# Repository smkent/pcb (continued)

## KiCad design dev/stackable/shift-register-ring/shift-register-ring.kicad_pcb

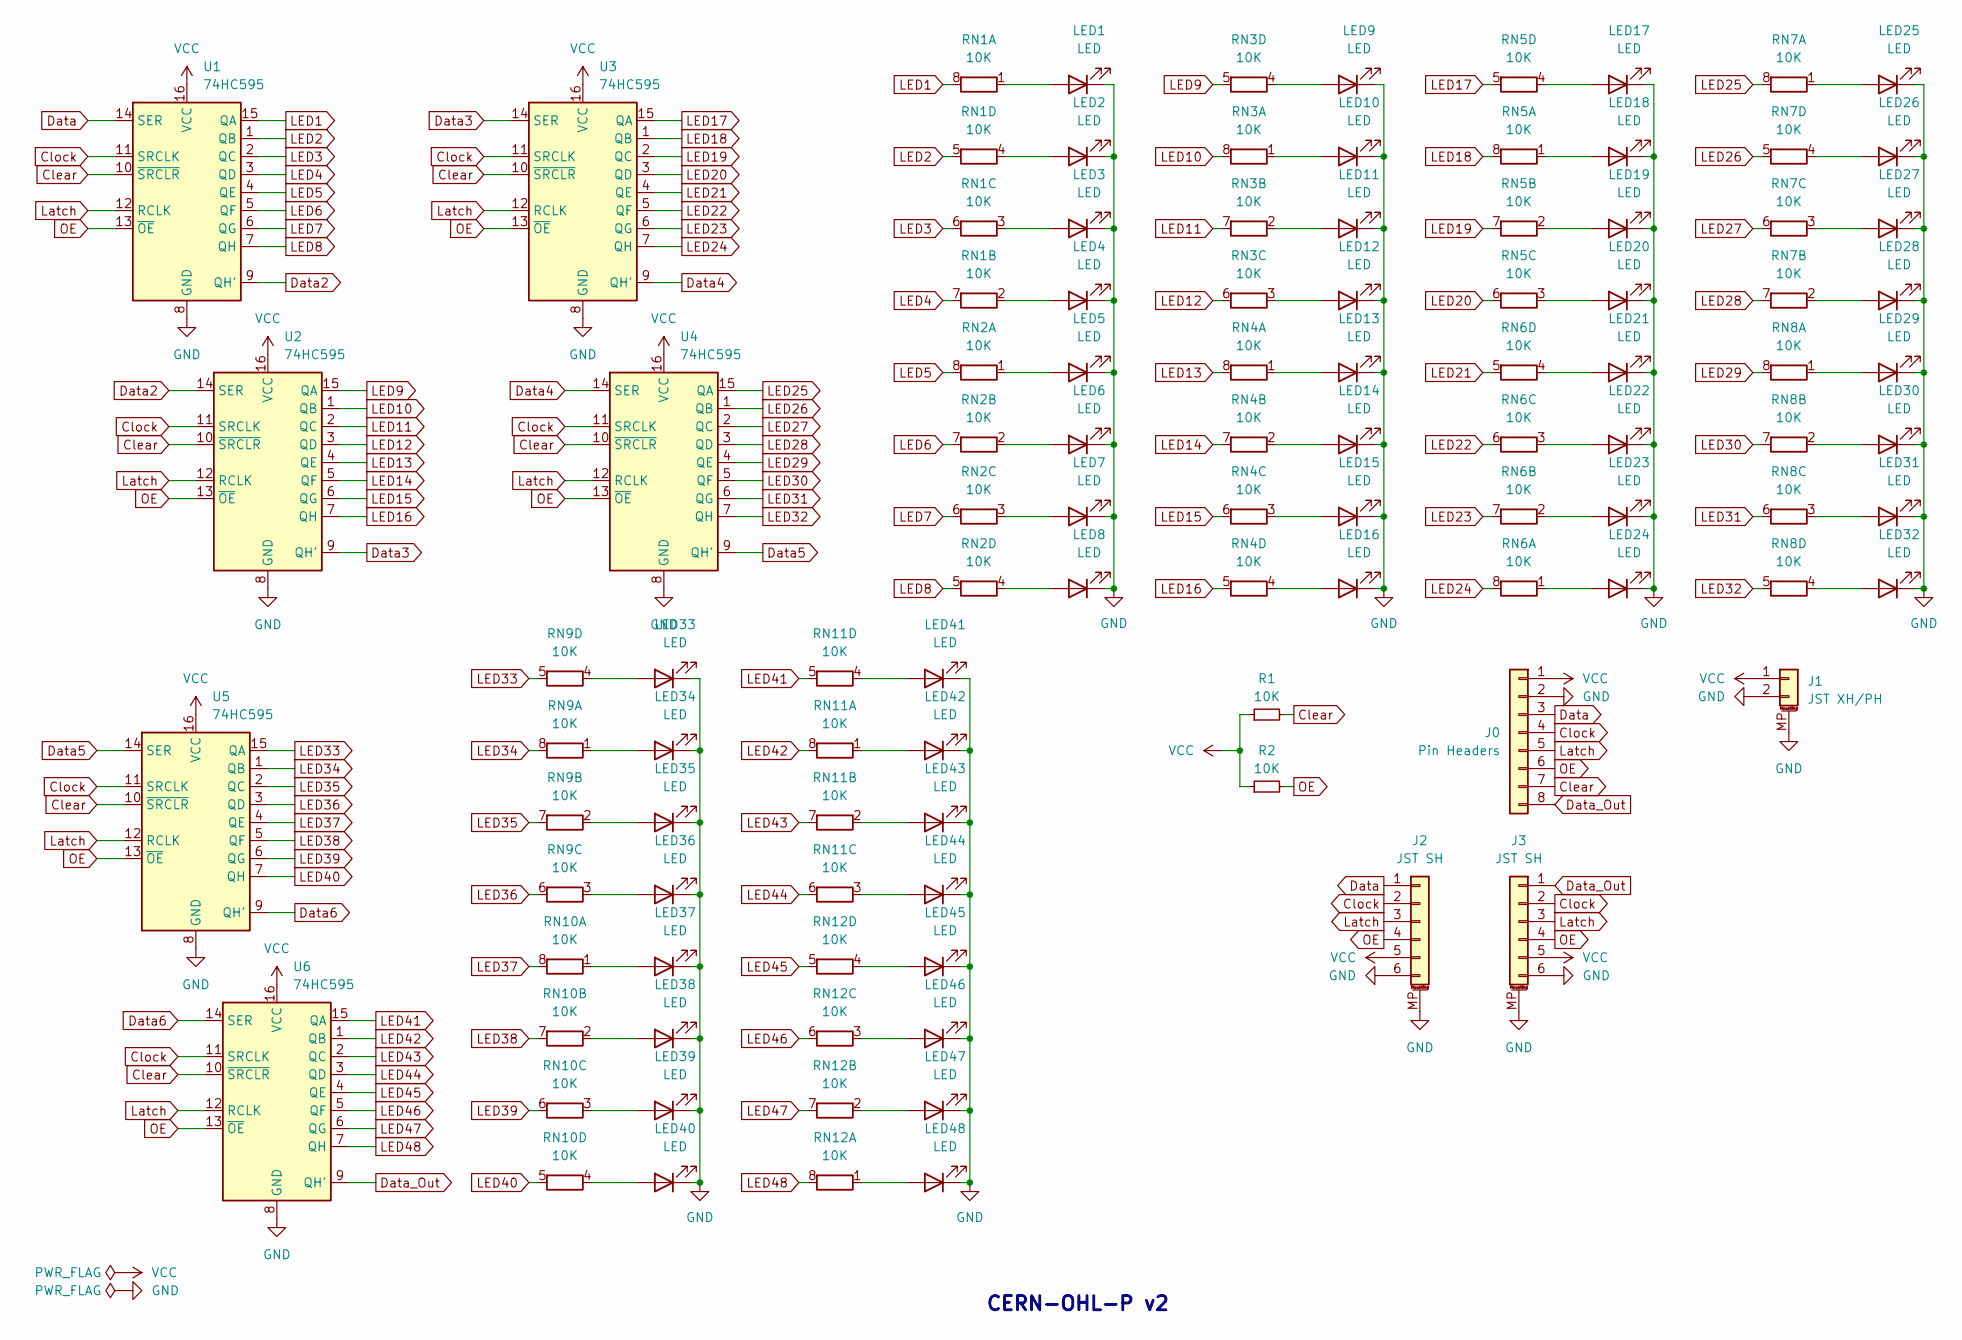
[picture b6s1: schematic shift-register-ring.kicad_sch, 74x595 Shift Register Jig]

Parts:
J0: Pin Headers; PinHeader_1x08_P2.54mm_Vertical_simple_pad2gnd
J1: JST XH/PH; Conn_Combo_JST-1x02-XH_PH-SMD-pad2gnd
J2, J3: JST SH; JST_SH_SM06B-SRSS-TB_1x06-1MP_P1.00mm_Horizontal
LED1, LED2, LED3, LED4, LED5, LED6, LED7, LED8, LED9, LED10, LED11, LED12, LED13, LED14, LED15, LED16, LED17, LED18, LED19, LED20, LED21, LED22, LED23, LED24, LED25, LED26, LED27, LED28, LED29, LED30, LED31, LED32, LED33, LED34, LED35, LED36, LED37, LED38, LED39, LED40, LED41, LED42, LED43, LED44, LED45, LED46, LED47, LED48: LED; LED_0603_1608Metric_Pad1.05x0.95mm_HandSolder_simple
R1, R2: 10K; R_0603_1608Metric_Pad0.98x0.95mm_HandSolder
RN1, RN2, RN3, RN4, RN5, RN6, RN7, RN8, RN9, RN10, RN11, RN12: 10K; R_Array_Convex_4x0603
U1, U2, U3, U4, U5, U6: 74HC595; SOIC-16_3.9x9.9mm_P1.27mm

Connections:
Clear: J0.7, R1.2, U1.10 (~SRCLR), U2.10 (~SRCLR), U3.10 (~SRCLR), U4.10 (~SRCLR), U5.10 (~SRCLR), U6.10 (~SRCLR)
Clock: J0.4, J2.2, J3.2, U1.11 (SRCLK), U2.11 (SRCLK), U3.11 (SRCLK), U4.11 (SRCLK), U5.11 (SRCLK), U6.11 (SRCLK)
Data: J0.3, J2.1, U1.14 (SER)
Data2: U1.9 (QH'), U2.14 (SER)
Data3: U2.9 (QH'), U3.14 (SER)
Data4: U3.9 (QH'), U4.14 (SER)
Data5: U4.9 (QH'), U5.14 (SER)
Data6: U5.9 (QH'), U6.14 (SER)
Data_Out: J0.8, J3.1, U6.9 (QH')
GND: J0.2, J1.2, J1.MP (MountPin), J2.6, J2.MP (MountPin), J3.6, J3.MP (MountPin), LED1.1 (K), LED2.1 (K), LED3.1 (K), LED4.1 (K), LED5.1 (K), LED6.1 (K), LED7.1 (K), LED8.1 (K), LED9.1 (K), LED10.1 (K), LED11.1 (K), LED12.1 (K), LED13.1 (K), LED14.1 (K), LED15.1 (K), LED16.1 (K), LED17.1 (K), LED18.1 (K), LED19.1 (K), LED20.1 (K), LED21.1 (K), LED22.1 (K), LED23.1 (K), LED24.1 (K), LED25.1 (K), LED26.1 (K), LED27.1 (K), LED28.1 (K), LED29.1 (K), LED30.1 (K), LED31.1 (K), LED32.1 (K), LED33.1 (K), LED34.1 (K), LED35.1 (K), LED36.1 (K), LED37.1 (K), LED38.1 (K), LED39.1 (K), LED40.1 (K), LED41.1 (K), LED42.1 (K), LED43.1 (K), LED44.1 (K), LED45.1 (K), LED46.1 (K), LED47.1 (K), LED48.1 (K), U1.8 (GND), U2.8 (GND), U3.8 (GND), U4.8 (GND), U5.8 (GND), U6.8 (GND)
LED1: RN1.8 (R1.2), U1.15 (QA)
LED2: RN1.5 (R4.2), U1.1 (QB)
LED3: RN1.6 (R3.2), U1.2 (QC)
LED4: RN1.7 (R2.2), U1.3 (QD)
LED5: RN2.8 (R1.2), U1.4 (QE)
LED6: RN2.7 (R2.2), U1.5 (QF)
LED7: RN2.6 (R3.2), U1.6 (QG)
LED8: RN2.5 (R4.2), U1.7 (QH)
LED9: RN3.5 (R4.2), U2.15 (QA)
LED10: RN3.8 (R1.2), U2.1 (QB)
LED11: RN3.7 (R2.2), U2.2 (QC)
LED12: RN3.6 (R3.2), U2.3 (QD)
LED13: RN4.8 (R1.2), U2.4 (QE)
LED14: RN4.7 (R2.2), U2.5 (QF)
LED15: RN4.6 (R3.2), U2.6 (QG)
LED16: RN4.5 (R4.2), U2.7 (QH)
LED17: RN5.5 (R4.2), U3.15 (QA)
LED18: RN5.8 (R1.2), U3.1 (QB)
LED19: RN5.7 (R2.2), U3.2 (QC)
LED20: RN5.6 (R3.2), U3.3 (QD)
LED21: RN6.5 (R4.2), U3.4 (QE)
LED22: RN6.6 (R3.2), U3.5 (QF)
LED23: RN6.7 (R2.2), U3.6 (QG)
LED24: RN6.8 (R1.2), U3.7 (QH)
LED25: RN7.8 (R1.2), U4.15 (QA)
LED26: RN7.5 (R4.2), U4.1 (QB)
LED27: RN7.6 (R3.2), U4.2 (QC)
LED28: RN7.7 (R2.2), U4.3 (QD)
LED29: RN8.8 (R1.2), U4.4 (QE)
LED30: RN8.7 (R2.2), U4.5 (QF)
LED31: RN8.6 (R3.2), U4.6 (QG)
LED32: RN8.5 (R4.2), U4.7 (QH)
LED33: RN9.5 (R4.2), U5.15 (QA)
LED34: RN9.8 (R1.2), U5.1 (QB)
LED35: RN9.7 (R2.2), U5.2 (QC)
LED36: RN9.6 (R3.2), U5.3 (QD)
LED37: RN10.8 (R1.2), U5.4 (QE)
LED38: RN10.7 (R2.2), U5.5 (QF)
LED39: RN10.6 (R3.2), U5.6 (QG)
LED40: RN10.5 (R4.2), U5.7 (QH)
LED41: RN11.5 (R4.2), U6.15 (QA)
LED42: RN11.8 (R1.2), U6.1 (QB)
LED43: RN11.7 (R2.2), U6.2 (QC)
LED44: RN11.6 (R3.2), U6.3 (QD)
LED45: RN12.5 (R4.2), U6.4 (QE)
LED46: RN12.6 (R3.2), U6.5 (QF)
LED47: RN12.7 (R2.2), U6.6 (QG)
LED48: RN12.8 (R1.2), U6.7 (QH)
Latch: J0.5, J2.3, J3.3, U1.12 (RCLK), U2.12 (RCLK), U3.12 (RCLK), U4.12 (RCLK), U5.12 (RCLK), U6.12 (RCLK)
unnamed: LED1.2 (A), RN1.1 (R1.1)
unnamed: LED2.2 (A), RN1.4 (R4.1)
unnamed: LED3.2 (A), RN1.3 (R3.1)
unnamed: LED4.2 (A), RN1.2 (R2.1)
unnamed: LED5.2 (A), RN2.1 (R1.1)
unnamed: LED6.2 (A), RN2.2 (R2.1)
unnamed: LED7.2 (A), RN2.3 (R3.1)
unnamed: LED8.2 (A), RN2.4 (R4.1)
unnamed: LED9.2 (A), RN3.4 (R4.1)
unnamed: LED10.2 (A), RN3.1 (R1.1)
unnamed: LED11.2 (A), RN3.2 (R2.1)
unnamed: LED12.2 (A), RN3.3 (R3.1)
unnamed: LED13.2 (A), RN4.1 (R1.1)
unnamed: LED14.2 (A), RN4.2 (R2.1)
unnamed: LED15.2 (A), RN4.3 (R3.1)
unnamed: LED16.2 (A), RN4.4 (R4.1)
unnamed: LED17.2 (A), RN5.4 (R4.1)
unnamed: LED18.2 (A), RN5.1 (R1.1)
unnamed: LED19.2 (A), RN5.2 (R2.1)
unnamed: LED20.2 (A), RN5.3 (R3.1)
unnamed: LED21.2 (A), RN6.4 (R4.1)
unnamed: LED22.2 (A), RN6.3 (R3.1)
unnamed: LED23.2 (A), RN6.2 (R2.1)
unnamed: LED24.2 (A), RN6.1 (R1.1)
unnamed: LED25.2 (A), RN7.1 (R1.1)
unnamed: LED26.2 (A), RN7.4 (R4.1)
unnamed: LED27.2 (A), RN7.3 (R3.1)
unnamed: LED28.2 (A), RN7.2 (R2.1)
unnamed: LED29.2 (A), RN8.1 (R1.1)
unnamed: LED30.2 (A), RN8.2 (R2.1)
unnamed: LED31.2 (A), RN8.3 (R3.1)
unnamed: LED32.2 (A), RN8.4 (R4.1)
unnamed: LED33.2 (A), RN9.4 (R4.1)
unnamed: LED34.2 (A), RN9.1 (R1.1)
unnamed: LED35.2 (A), RN9.2 (R2.1)
unnamed: LED36.2 (A), RN9.3 (R3.1)
unnamed: LED37.2 (A), RN10.1 (R1.1)
unnamed: LED38.2 (A), RN10.2 (R2.1)
unnamed: LED39.2 (A), RN10.3 (R3.1)
unnamed: LED40.2 (A), RN10.4 (R4.1)
unnamed: LED41.2 (A), RN11.4 (R4.1)
unnamed: LED42.2 (A), RN11.1 (R1.1)
unnamed: LED43.2 (A), RN11.2 (R2.1)
unnamed: LED44.2 (A), RN11.3 (R3.1)
unnamed: LED45.2 (A), RN12.4 (R4.1)
unnamed: LED46.2 (A), RN12.3 (R3.1)
unnamed: LED47.2 (A), RN12.2 (R2.1)
unnamed: LED48.2 (A), RN12.1 (R1.1)
OE: J0.6, J2.4, J3.4, R2.2, U1.13 (~OE), U2.13 (~OE), U3.13 (~OE), U4.13 (~OE), U5.13 (~OE), U6.13 (~OE)
VCC: J0.1, J1.1, J2.5, J3.5, R1.1, R2.1, U1.16 (VCC), U2.16 (VCC), U3.16 (VCC), U4.16 (VCC), U5.16 (VCC), U6.16 (VCC)

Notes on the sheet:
CERN-OHL-P v2

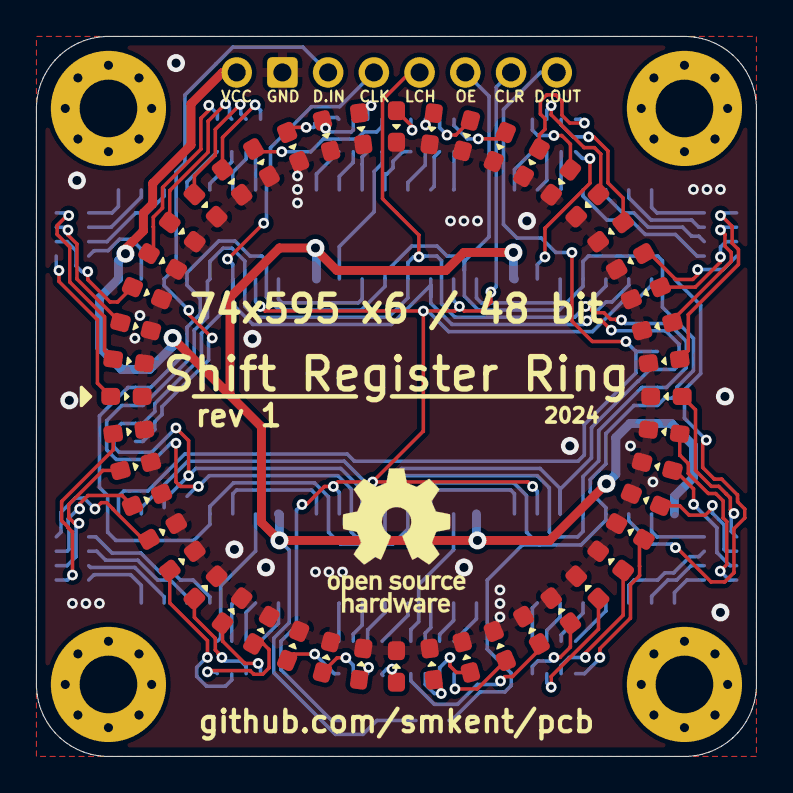
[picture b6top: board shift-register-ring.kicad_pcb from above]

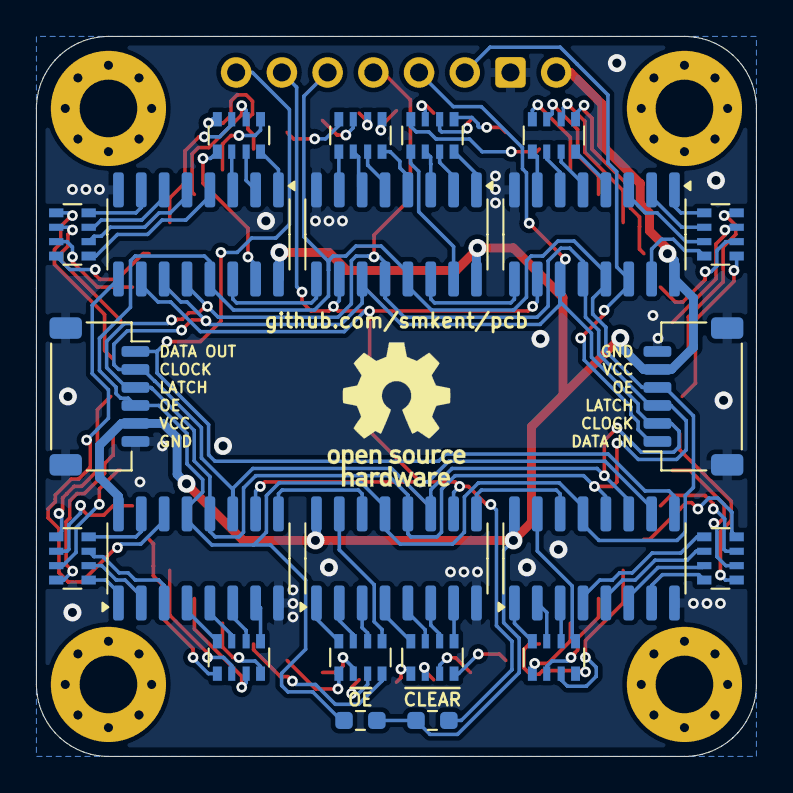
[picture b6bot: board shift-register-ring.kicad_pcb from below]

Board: 2 copper layers, 40.0 x 40.0 mm, 71 parts (23 on the bottom side), 109 nets.

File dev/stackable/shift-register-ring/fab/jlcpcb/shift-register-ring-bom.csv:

Comment,Designator,Footprint,LCSC
LED,"LED1,LED2,LED3,LED4,LED5,LED6,LED7,LED8,LED9,LED10,LED11,LED12,LED13,LED14,LED15,LED16,LED17,LED18,LED19,LED20,LED21,LED22,LED23,LED24,LED25,LED26,LED27,LED28,LED29,LED30,LED31,LED32,LED33,LED34,LED35,LED36,LED37,LED38,LED39,LED40,LED41,LED42,LED43,LED44,LED45,LED46,LED47,LED48",custom:LED_0603_1608Metric_Pad1.05x0.95mm_HandSolder_simple,
10K,"RN1,RN2,RN3,RN4,RN5,RN6,RN7,RN8,RN9,RN10,RN11,RN12",Resistor_SMD:R_Array_Convex_4x0603,
74HC595,"U1,U2,U3,U4,U5,U6",Package_SO:SOIC-16_3.9x9.9mm_P1.27mm,
JST SH,"J2,J3",connectors:JST_SH_SM06B-SRSS-TB_1x06-1MP_P1.00mm_Horizontal,
10K,"R1,R2",Resistor_SMD:R_0603_1608Metric_Pad0.98x0.95mm_HandSolder,
Pin Headers,J0,custom:PinHeader_1x08_P2.54mm_Vertical_simple_pad2gnd,

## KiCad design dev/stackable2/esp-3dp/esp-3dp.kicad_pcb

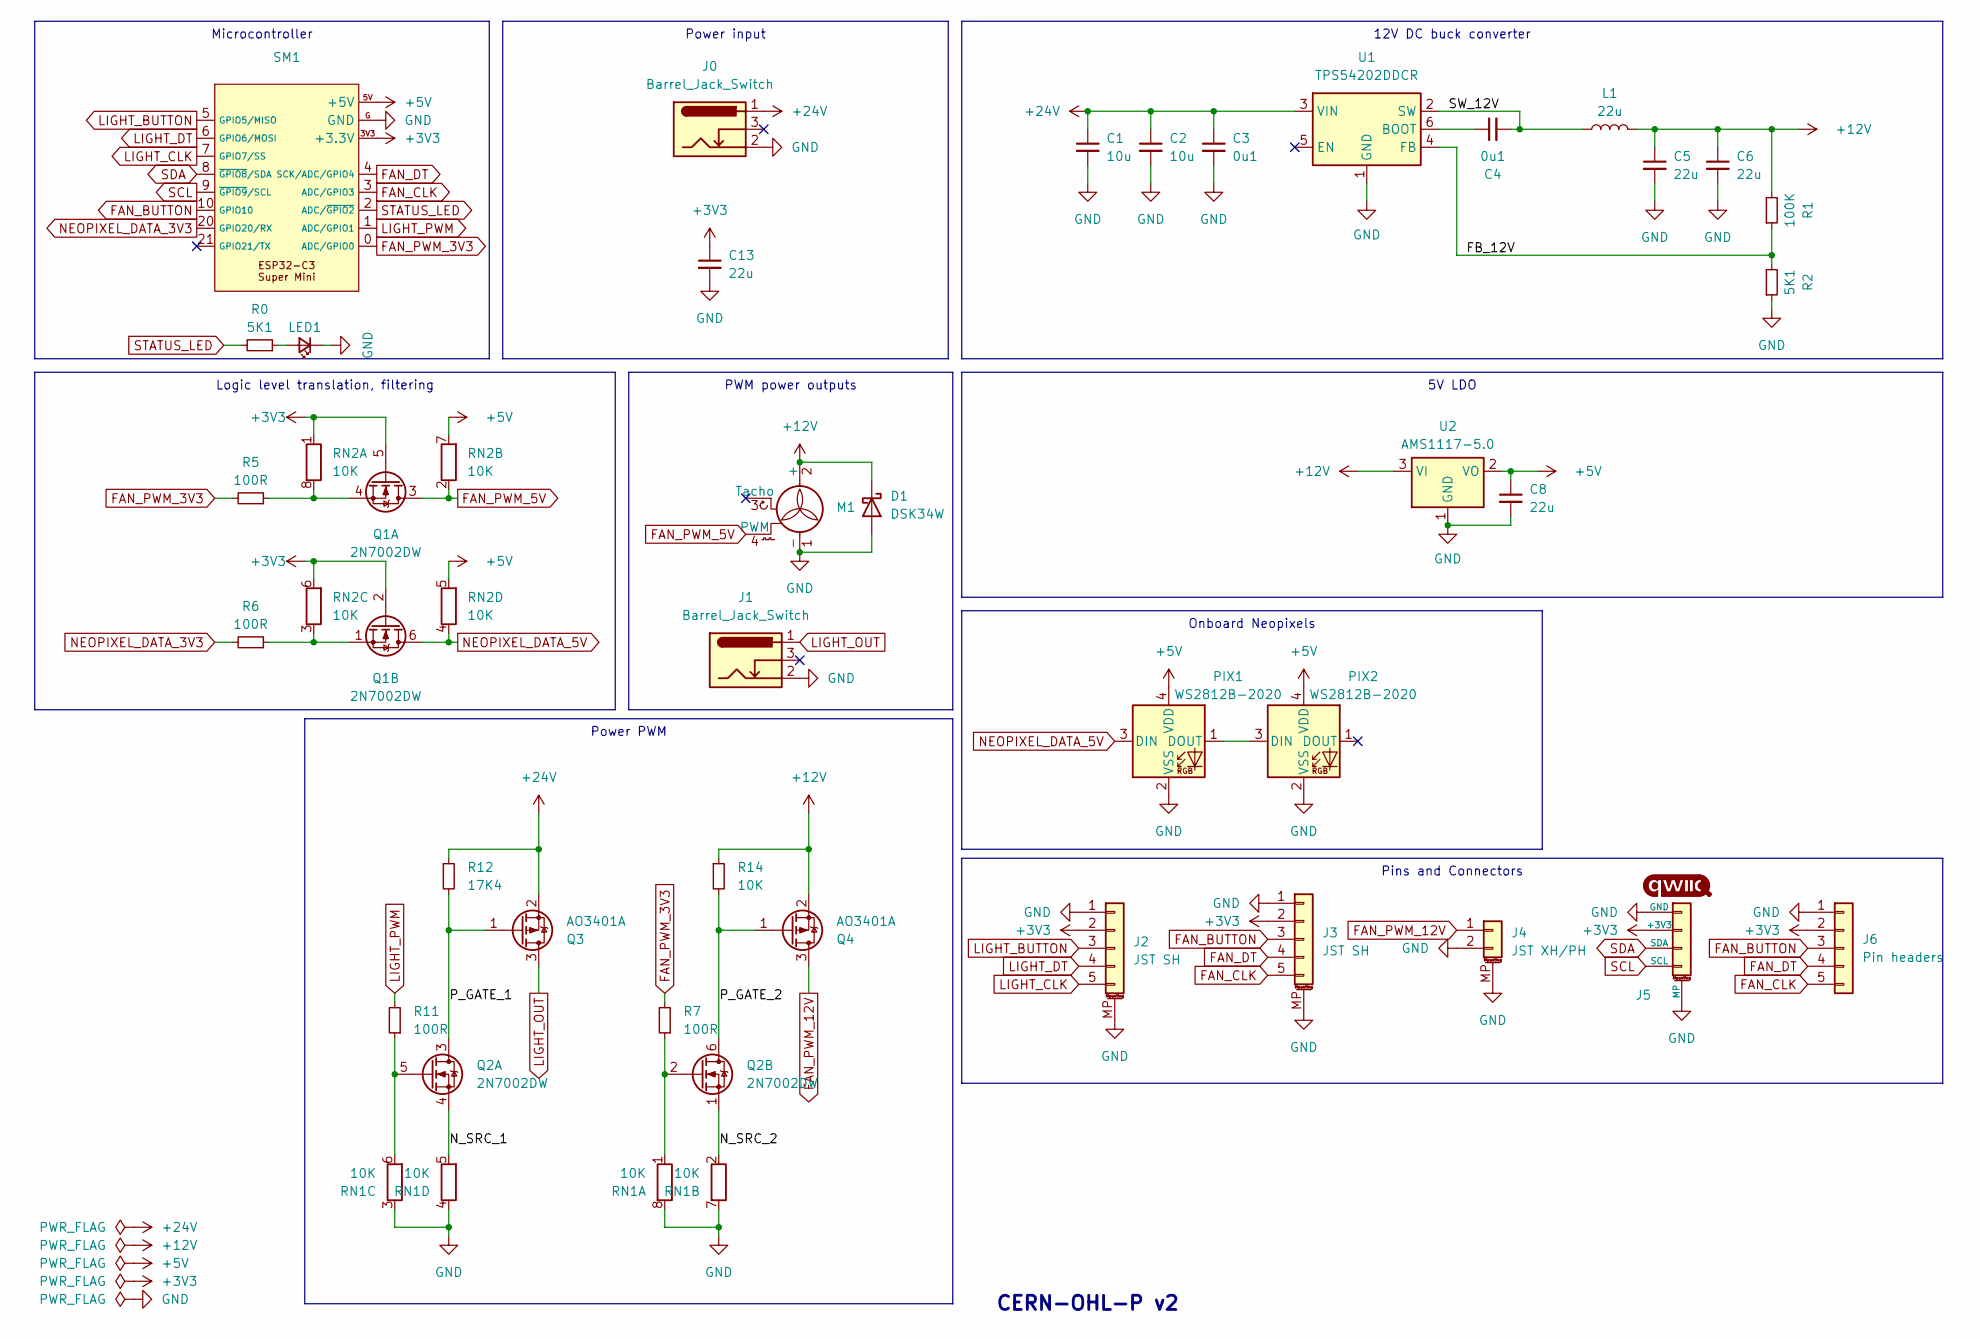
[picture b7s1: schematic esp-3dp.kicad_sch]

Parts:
C1, C2: 10u; C_0603_1608Metric_Pad1.08x0.95mm_HandSolder
C3, C4: 0u1; C_0603_1608Metric_Pad1.08x0.95mm_HandSolder
C5, C6, C8: 22u; C_0805_2012Metric_Pad1.18x1.45mm_HandSolder
C13: 22u; C_0603_1608Metric_Pad1.08x0.95mm_HandSolder
D1: DSK34W; D_SOD-123F_simple
J0, J1: Barrel_Jack_Switch; DC-IN_DC-050-2.0-BB_rev2
J2, J3: JST SH; JST_SH_SM05B-SRSS-TB_1x05-1MP_P1.00mm_Horizontal
J4: JST XH/PH; Conn_Combo_JST-1x02-XH_PH-SMD-pad2gnd
J5: Qwiic; Qwiic-SMD-horizontal-logo-bottom-pinout
J6: Pin headers; PinHeader_1x05_P2.54mm_Vertical_simple_pad1gnd
L1: 22u; IND-SMD_L7.0-W6.6; LCSC Part C22471106
LED1: LED_Small; LED_0603_1608Metric_Pad1.05x0.95mm_HandSolder_simple
M1: KF2510; FanPinHeader_1x04_P2.54mm_Horizontal
PIX1, PIX2: WS2812B-2020; LED-SMD_4P-L2.0-W2.0-BR-1
Q1, Q2: 2N7002DW; SOT-363_SC-70-6; LCSC Part C5190214
Q3, Q4: AO3401A; SOT-23
R0, R2: 5K1; R_0603_1608Metric_Pad0.98x0.95mm_HandSolder
R1: 100K; R_0603_1608Metric_Pad0.98x0.95mm_HandSolder
R5, R6, R7, R11: 100R; R_0603_1608Metric_Pad0.98x0.95mm_HandSolder
R12: 17K4; R_0603_1608Metric_Pad0.98x0.95mm_HandSolder
R14: 10K; R_0603_1608Metric_Pad0.98x0.95mm_HandSolder
RN1, RN2: 10K; R_Array_Convex_4x0603
SM1: ESP32-C3-Super-Mini-Castellated-SMD-only
U1: TPS54202DDCR; SOT-23-6; LCSC Part C191884
U2: AMS1117-5.0; SOT-223-3_TabPin2

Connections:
+3V3: C13.1, J2.2, J3.2, J5.2 (+3V3), J6.2, Q1.2 (G), Q1.5 (G), RN2.1 (R1.1), RN2.6 (R3.2), SM1.3V3 (+3.3V)
+5V: C8.1, PIX1.4 (VDD), PIX2.4 (VDD), RN2.5 (R4.2), RN2.7 (R2.2), SM1.5V (+5V), U2.2 (VO)
+12V: C5.1, C6.1, D1.1 (K), L1.2, M1.2 (+), Q4.2 (S), R1.2, R14.1, U2.3 (VI)
+24V: C1.1, C2.1, C3.1, J0.1, Q3.2 (S), R12.1, U1.3 (VIN)
/FB_12V: R1.1, R2.2, U1.4 (FB)
/N_SRC_1: Q2.4 (S), RN1.5 (R4.2)
/N_SRC_2: Q2.1 (S), RN1.2 (R2.1)
/P_GATE_1: Q2.3 (D), Q3.1 (G), R12.2
/P_GATE_2: Q2.6 (D), Q4.1 (G), R14.2
/SW_12V: C4.2, L1.1, U1.2 (SW)
FAN_BUTTON: J3.3, J6.3, SM1.10 (GPIO10)
FAN_CLK: J3.5, J6.5, SM1.3 (ADC/GPIO3)
FAN_DT: J3.4, J6.4, SM1.4 (SCK/ADC/GPIO4)
FAN_PWM_3V3: R5.2, R7.2, SM1.0 (ADC/GPIO0)
FAN_PWM_5V: M1.4 (PWM), Q1.3 (D), RN2.2 (R2.1)
FAN_PWM_12V: J4.1, Q4.3 (D)
GND: C1.2, C2.2, C3.2, C5.2, C6.2, C8.2, C13.2, D1.2 (A), J0.2, J1.2, J2.1, J2.MP (MountPin), J3.1, J3.MP (MountPin), J4.2, J4.MP (MountPin), J5.1 (GND), J5.MP, J6.1, LED1.1 (K), M1.1 (-), PIX1.2 (VSS), PIX2.2 (VSS), R2.1, RN1.3 (R3.1), RN1.4 (R4.1), RN1.7 (R2.2), RN1.8 (R1.2), SM1.G (GND), U1.1 (GND), U2.1 (GND)
LIGHT_BUTTON: J2.3, SM1.5 (GPIO5/MISO)
LIGHT_CLK: J2.5, SM1.7 (GPIO7/SS)
LIGHT_DT: J2.4, SM1.6 (GPIO6/MOSI)
LIGHT_OUT: J1.1, Q3.3 (D)
LIGHT_PWM: R11.2, SM1.1 (ADC/GPIO1)
NEOPIXEL_DATA_3V3: R6.2, SM1.20 (GPIO20/RX)
NEOPIXEL_DATA_5V: PIX1.3 (DIN), Q1.6 (D), RN2.4 (R4.1)
unnamed: LED1.2 (A), R0.1
unnamed: PIX1.1 (DOUT), PIX2.3 (DIN)
unnamed: Q1.4 (S), R5.1, RN2.8 (R1.2)
unnamed: Q1.1 (S), R6.1, RN2.3 (R3.1)
unnamed: Q2.5 (G), R11.1, RN1.6 (R3.2)
unnamed: Q2.2 (G), R7.1, RN1.1 (R1.1)
unnamed: C4.1, U1.6 (BOOT)
SCL: J5.4 (SCL), SM1.9 (~GPIO9/SCL)
SDA: J5.3 (SDA), SM1.8 (~GPIO8/SDA)
STATUS_LED: R0.2, SM1.2 (ADC/~GPIO2)

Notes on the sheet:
Power input
12V DC buck converter
5V LDO
Microcontroller
PWM power outputs
Onboard Neopixels
Pins and Connectors
Logic level translation, filtering
Power PWM
CERN-OHL-P v2

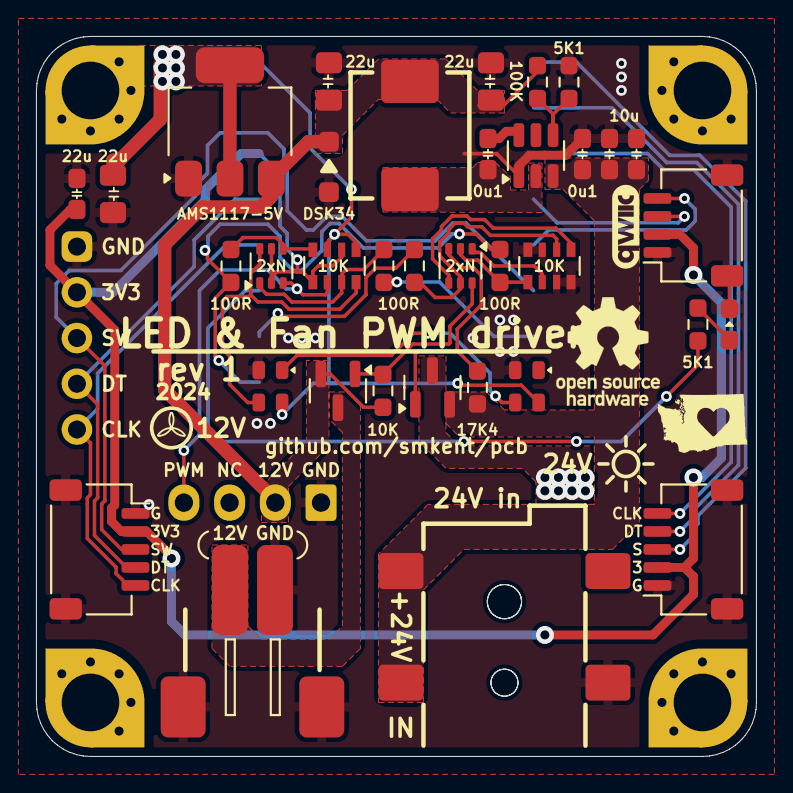
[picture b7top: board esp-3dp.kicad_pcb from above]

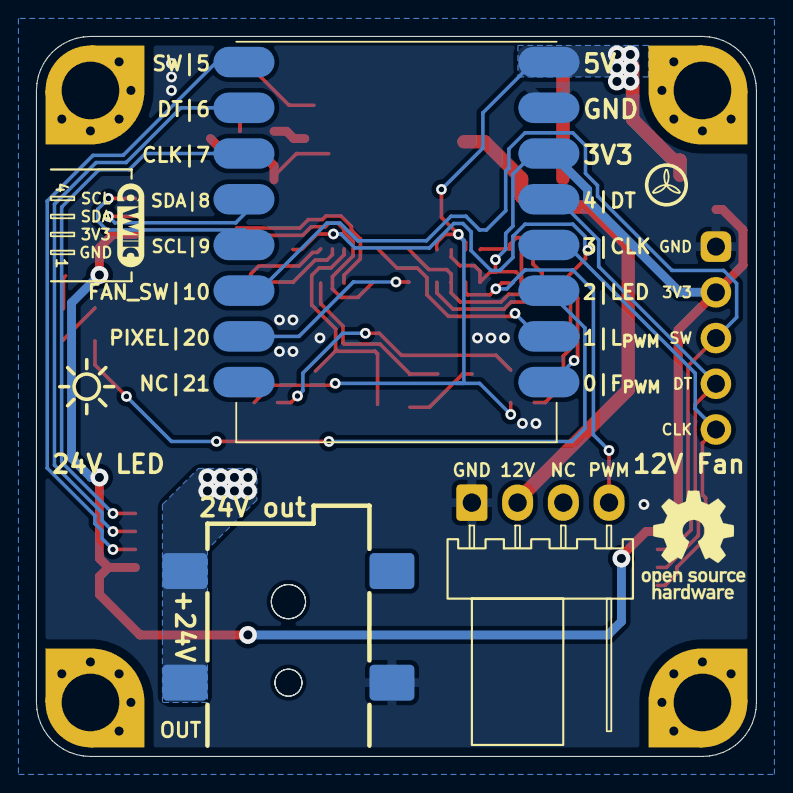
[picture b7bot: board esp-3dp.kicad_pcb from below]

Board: 2 copper layers, 40.0 x 40.0 mm, 43 parts (4 on the bottom side), 34 nets.

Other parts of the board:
MH_NE: MountingHole_3.2mm_M3_Pad_Via_corner_compact
MH_NW: MountingHole_3.2mm_M3_Pad_Via_corner_compact
MH_SE: MountingHole_3.2mm_M3_Pad_Via_corner_compact
MH_SW: MountingHole_3.2mm_M3_Pad_Via_corner_compact

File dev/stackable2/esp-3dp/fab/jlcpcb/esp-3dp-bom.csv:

Comment,Designator,Footprint,LCSC
22u,"C5,C6,C8",custom:C_0805_2012Metric_Pad1.18x1.45mm_HandSolder,
5K1,"R0,R2",Resistor_SMD:R_0603_1608Metric_Pad0.98x0.95mm_HandSolder,
17K4,R12,Resistor_SMD:R_0603_1608Metric_Pad0.98x0.95mm_HandSolder,
100K,R1,Resistor_SMD:R_0603_1608Metric_Pad0.98x0.95mm_HandSolder,
WS2812B-2020,"PIX1,PIX2",lcsc:LED-SMD_4P-L2.0-W2.0-BR-1,
10u,"C1,C2",custom:C_0603_1608Metric_Pad1.08x0.95mm_HandSolder,
Barrel_Jack_Switch,"J0,J1",custom:DC-IN_DC-050-2.0-BB_rev2,
100R,"R5,R6,R7,R11",Resistor_SMD:R_0603_1608Metric_Pad0.98x0.95mm_HandSolder,
~,SM1,modules:ESP32-C3-Super-Mini-Castellated-SMD-only,
AMS1117-5.0,U2,Package_TO_SOT_SMD:SOT-223-3_TabPin2,
0u1,"C3,C4",custom:C_0603_1608Metric_Pad1.08x0.95mm_HandSolder,
DSK34W,D1,custom:D_SOD-123F_simple,
KF2510,M1,connectors:FanPinHeader_1x04_P2.54mm_Horizontal,
AO3401A,"Q3,Q4",Package_TO_SOT_SMD:SOT-23,
2N7002DW,"Q1,Q2",Package_TO_SOT_SMD:SOT-363_SC-70-6,C5190214
Pin headers,J6,custom:PinHeader_1x05_P2.54mm_Vertical_simple_pad1gnd,
Qwiic,J5,connectors:Qwiic-SMD-horizontal-logo-bottom-pinout,
LED_Small,LED1,custom:LED_0603_1608Metric_Pad1.05x0.95mm_HandSolder_simple,
22u,C13,custom:C_0603_1608Metric_Pad1.08x0.95mm_HandSolder,
TPS54202DDCR,U1,Package_TO_SOT_SMD:SOT-23-6,C191884
JST SH,"J2,J3",connectors:JST_SH_SM05B-SRSS-TB_1x05-1MP_P1.00mm_Horizontal,
10K,R14,Resistor_SMD:R_0603_1608Metric_Pad0.98x0.95mm_HandSolder,
JST XH/PH,J4,custom:Conn_Combo_JST-1x02-XH_PH-SMD-pad2gnd,
22u,L1,lcsc:IND-SMD_L7.0-W6.6,C22471106
10K,"RN1,RN2",Resistor_SMD:R_Array_Convex_4x0603,
